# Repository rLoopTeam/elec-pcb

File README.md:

# elec-pcb
All PCB designs for rLoop in Altium Designer 13 format.

Altium Viewer License is needed: http://www.altium.com/altium-designer-viewer
CAD files in Inventor 2013 format and .step.

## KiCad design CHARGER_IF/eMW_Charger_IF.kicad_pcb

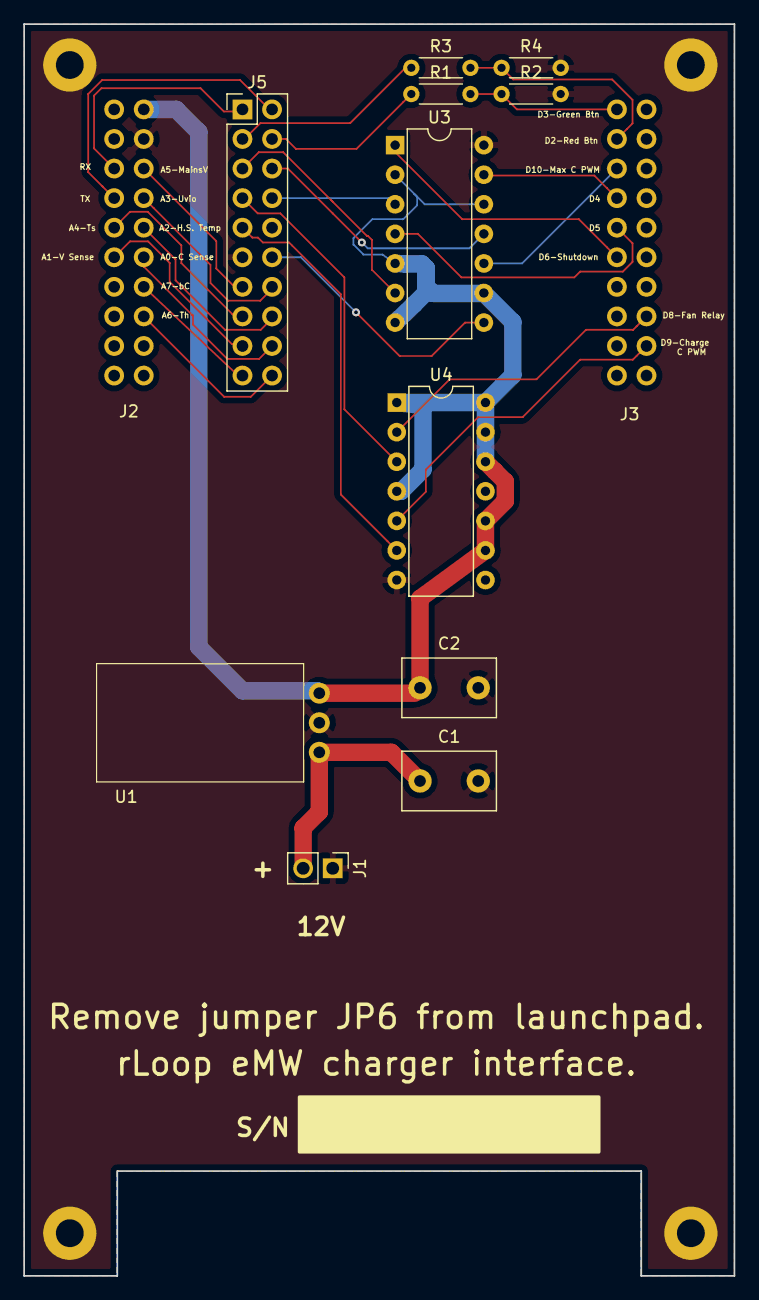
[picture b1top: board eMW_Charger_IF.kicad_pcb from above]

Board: 2 copper layers, 61.0 x 107.5 mm, 13 parts (0 on the bottom side), 29 nets.

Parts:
C1: 10 uF / 25V / TH; C_Disc_D8.0mm_W5.0mm_P5.00mm
C2: 22 uF / 16V / TH; C_Disc_D8.0mm_W5.0mm_P5.00mm
J1: CONN_01X02; Pin_Header_Straight_1x02_Pitch2.54mm
J2: Booster_J1_J3; 6-146256-0
J3: Booster_J4_J2; 6-146256-0_40-31_20_11
J5: CONN_02X10; Pin_Header_Straight_2x10_Pitch2.54mm
R1, R3: 10k / 10% / TH; R_Axial_DIN0204_L3.6mm_D1.6mm_P5.08mm_Horizontal
R2, R4: 20k / 10% / TH; R_Axial_DIN0204_L3.6mm_D1.6mm_P5.08mm_Horizontal
U1: V7805-2000R
U3, U4: SN74ACT08N; DIP-14_W7.62mm

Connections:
+5V: C2.1, J2.21, U1.3, U3.2, U3.5, U3.7, U3.9, U3.12, U4.1, U4.4, U4.9, U4.10, U4.12, U4.13, U4.14
+12V: C1.1, J1.2, U1.1
GND: C1.2, C2.2, J1.1, J2.22, J5.10, J5.11, R2.2, R4.2, U1.2, U3.14, U4.7
unnamed: J2.3, J5.1
unnamed: J2.4, J5.2
unnamed: J2.5, J5.15
unnamed: J2.6, J5.17
unnamed: J2.23, J5.13
unnamed: J2.24, J5.14
unnamed: J2.25, J5.16
unnamed: J2.26, J5.18
unnamed: J2.27, J5.19
unnamed: J2.28, J5.20
unnamed: J3.12, U4.5
unnamed: J3.13, U4.2
unnamed: J3.35, U3.1
unnamed: J3.36, U3.4
unnamed: J3.37, U3.13
unnamed: J3.38, U3.10
unnamed: J3.39, R3.2, R4.1
unnamed: J3.40, R1.2, R2.1
unnamed: J5.3, R3.1
unnamed: J5.4, R1.1
unnamed: J5.5, U3.6
unnamed: J5.6, U3.11
unnamed: J5.7, U4.3
unnamed: J5.8, U3.3
unnamed: J5.9, U4.6
unnamed: J5.12, U3.8

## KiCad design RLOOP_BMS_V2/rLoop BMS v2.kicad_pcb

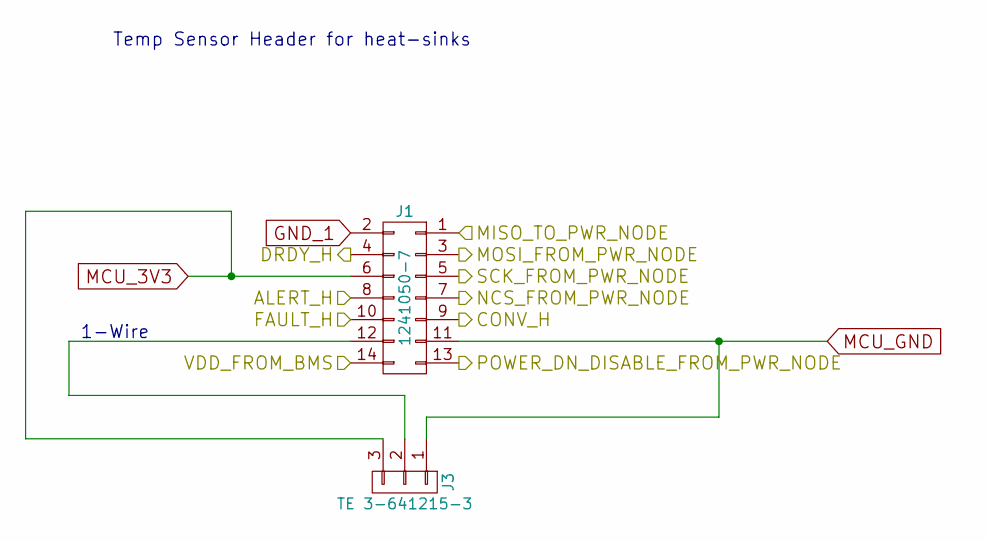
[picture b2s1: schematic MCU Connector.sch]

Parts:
J1: 1241050-7; Pin_Header_Straight_2x07_Pitch2.54mm_SMD_MIRROR
J3: TE 3-641215-3; 3-641215-3_3Pin_Latching_Header

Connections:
/CONTROLLER 1/ALERT_H: J1.8; also elsewhere on the board
/CONTROLLER 1/CONV_H: J1.9; also elsewhere on the board
/CONTROLLER 1/CS_H: J1.7; also elsewhere on the board
/CONTROLLER 1/DRDY_H: J1.4; also elsewhere on the board
/CONTROLLER 1/FAULT_H: J1.10; also elsewhere on the board
/ISO POWER/5V_ISO: J1.14; also elsewhere on the board
/ISO POWER/COMMS_EN: J1.13; also elsewhere on the board
/MCU Connector/MISO_TO_PWR_NODE: J1.1; also elsewhere on the board
/MCU Connector/MOSI_FROM_PWR_NODE: J1.3; also elsewhere on the board
/MCU Connector/SCK_FROM_PWR_NODE: J1.5; also elsewhere on the board
GND_1: J1.2; also elsewhere on the board
MCU_3V3: J1.6, J3.3; also elsewhere on the board
MCU_GND: J1.11, J3.1; also elsewhere on the board
unnamed: J1.12, J3.2

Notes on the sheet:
1-Wire
Temp Sensor Header for heat-sinks

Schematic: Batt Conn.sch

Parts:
J2: 2-640387-0; TE_2-640387-0

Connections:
/DISCHARGE_1/CELL_1: J2.2; also elsewhere on the board
/DISCHARGE_1/CELL_2: J2.3; also elsewhere on the board
/DISCHARGE_1/CELL_3: J2.4; also elsewhere on the board
/DISCHARGE_1/CELL_4: J2.5; also elsewhere on the board
/DISCHARGE_1/CELL_5: J2.6; also elsewhere on the board
/DISCHARGE_2/CELL_1: J2.8; also elsewhere on the board
/DISCHARGE_2/CELL_2: J2.9; also elsewhere on the board
/DISCHARGE_2/CELL_3: J2.10; also elsewhere on the board
GND_1: J2.1; also elsewhere on the board
GND_2: J2.7; also elsewhere on the board

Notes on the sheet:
Cell 0 is the negative terminal of the battery pack.

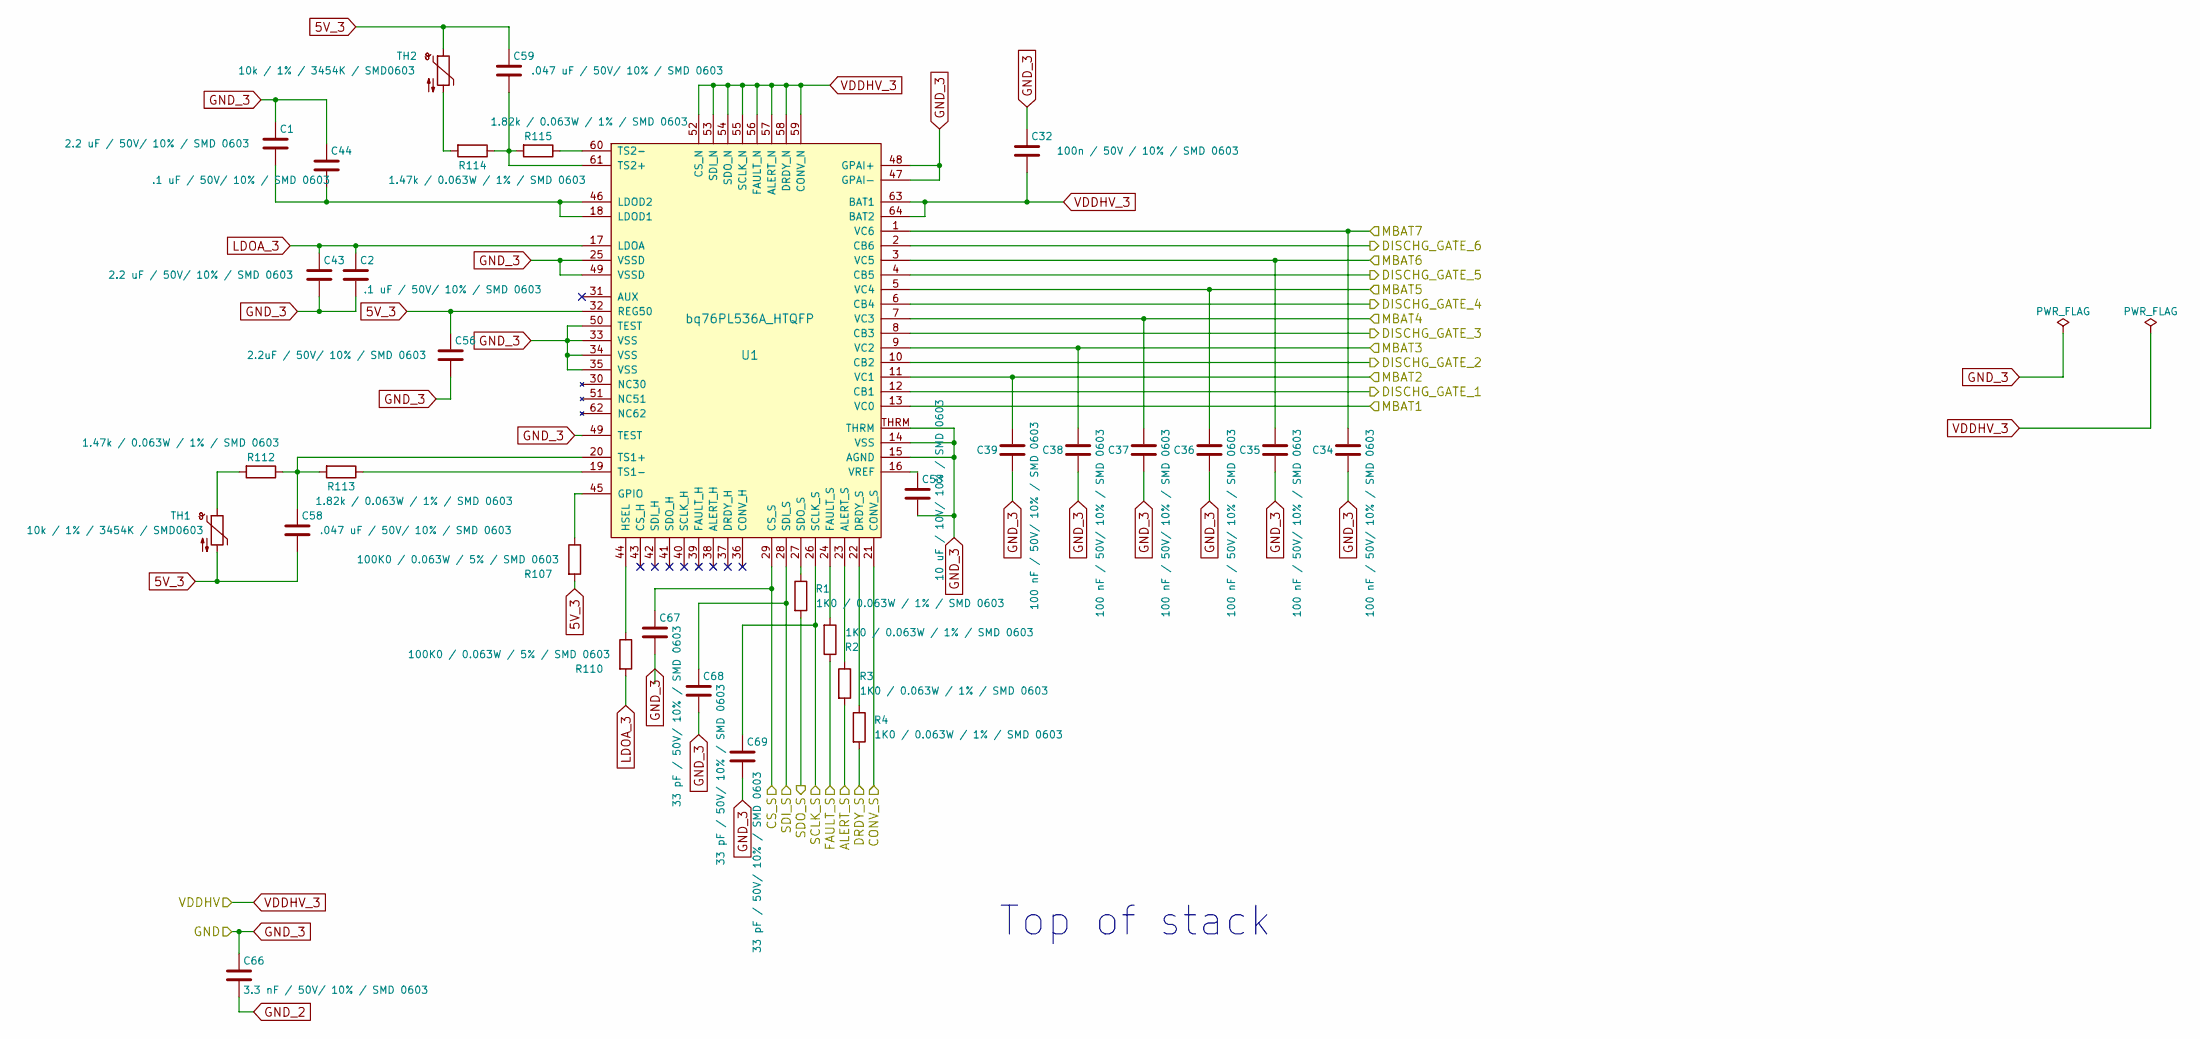
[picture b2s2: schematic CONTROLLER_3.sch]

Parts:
C1, C43: 2.2 uF / 50V/ 10% / SMD 0603; C_0603
C2, C44: .1 uF / 50V/ 10% / SMD 0603; C_0603
C32: 100n / 50V / 10% / SMD 0603; C_0603
C34, C35, C36, C37, C38, C39: 100 nF / 50V/ 10% / SMD 0603; C_0603
C53: 10 uF / 10V/ 10% / SMD 0603; C_0603
C56: 2.2uF / 50V/ 10% / SMD 0603; C_0603
C58, C59: .047 uF / 50V/ 10% / SMD 0603; C_0603
C66: 3.3 nF / 50V/ 10% / SMD 0603; C_0603
C67, C68, C69: 33 pF / 50V/ 10% / SMD 0603; C_0603
R1, R2, R3, R4: 1K0 / 0.063W / 1% / SMD 0603; R_0603
R107, R110: 100K0 / 0.063W / 5% / SMD 0603; R_0603
R112, R114: 1.47k / 0.063W / 1% / SMD 0603; R_0603
R113, R115: 1.82k / 0.063W / 1% / SMD 0603; R_0603
TH1, TH2: 10k / 1% / 3454K / SMD0603; R_0603
U1: bq76PL536A_HTQFP; bq76pl536a

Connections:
5V_3: C56.1, C58.2, C59.1, R107.2, TH1.2, TH2.1, U1.32 (REG50)
/CONTROLLER 2/ALERT_N: R3.2; also elsewhere on the board
/CONTROLLER 2/CONV_N: U1.21 (CONV_S); also elsewhere on the board
/CONTROLLER 2/CS_N: C67.1, U1.29 (CS_S); also elsewhere on the board
/CONTROLLER 2/DRDY_N: R4.2; also elsewhere on the board
/CONTROLLER 2/FAULT_N: R2.1; also elsewhere on the board
/CONTROLLER 2/SCLK_N: C69.1, U1.26 (SCLK_S); also elsewhere on the board
/CONTROLLER 2/SDI_N: C68.1, U1.28 (SDI_S); also elsewhere on the board
/CONTROLLER 2/SDO_N: R1.2; also elsewhere on the board
/CONTROLLER 3/MBAT2: C39.1, U1.11 (VC1); also elsewhere on the board
/CONTROLLER 3/MBAT3: C38.1, U1.9 (VC2); also elsewhere on the board
/CONTROLLER 3/MBAT4: C37.1, U1.7 (VC3); also elsewhere on the board
/CONTROLLER 3/MBAT5: C36.1, U1.5 (VC4); also elsewhere on the board
/CONTROLLER 3/MBAT6: C35.1, U1.3 (VC5); also elsewhere on the board
/CONTROLLER 3/MBAT7: C34.1, U1.1 (VC6); also elsewhere on the board
/DISCHARGE_3/DISCHARGE_1: U1.12 (CB1); also elsewhere on the board
/DISCHARGE_3/DISCHARGE_2: U1.10 (CB2); also elsewhere on the board
/DISCHARGE_3/DISCHARGE_3: U1.8 (CB3); also elsewhere on the board
/DISCHARGE_3/DISCHARGE_4: U1.6 (CB4); also elsewhere on the board
/DISCHARGE_3/DISCHARGE_5: U1.4 (CB5); also elsewhere on the board
/DISCHARGE_3/DISCHARGE_6: U1.2 (CB6); also elsewhere on the board
GND_2: C66.2; also elsewhere on the board
GND_3: C1.1, C2.2, C32.1, C34.2, C35.2, C36.2, C37.2, C38.2, C39.2, C43.2, C44.1, C53.2, C56.2, C66.1, C67.2, C68.2, C69.2, U1.13 (VC0), U1.14 (VSS), U1.15 (AGND), U1.25 (VSSD), U1.33 (VSS), U1.34 (VSS), U1.35 (VSS), U1.47 (GPAI-), U1.48 (GPAI+), U1.49 (TEST), U1.50 (TEST), U1.THRM; also elsewhere on the board
LDOA_3: C2.1, C43.1, R110.2, U1.17 (LDOA)
unnamed: C1.2, C44.2, U1.18 (LDOD1), U1.46 (LDOD2)
unnamed: C53.1, U1.16 (VREF)
unnamed: C58.1, R112.1, R113.2, U1.20 (TS1+)
unnamed: C59.2, R114.1, R115.2, U1.61 (TS2+)
unnamed: R1.1, U1.27 (SDO_S)
unnamed: R2.2, U1.24 (FAULT_S)
unnamed: R3.1, U1.23 (ALERT_S)
unnamed: R4.1, U1.22 (DRDY_S)
unnamed: R107.1, U1.45 (GPIO)
unnamed: R110.1, U1.44 (HSEL)
unnamed: R112.2, TH1.1
unnamed: R113.1, U1.19 (TS1-)
unnamed: R114.2, TH2.2
unnamed: R115.1, U1.60 (TS2-)
VDDHV_3: C32.2, U1.52 (CS_N), U1.53 (SDI_N), U1.54 (SDO_N), U1.55 (SCLK_N), U1.56 (FAULT_N), U1.57 (ALERT_N), U1.58 (DRDY_N), U1.59 (CONV_N), U1.63 (BAT1), U1.64 (BAT2); also elsewhere on the board

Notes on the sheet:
Top of stack

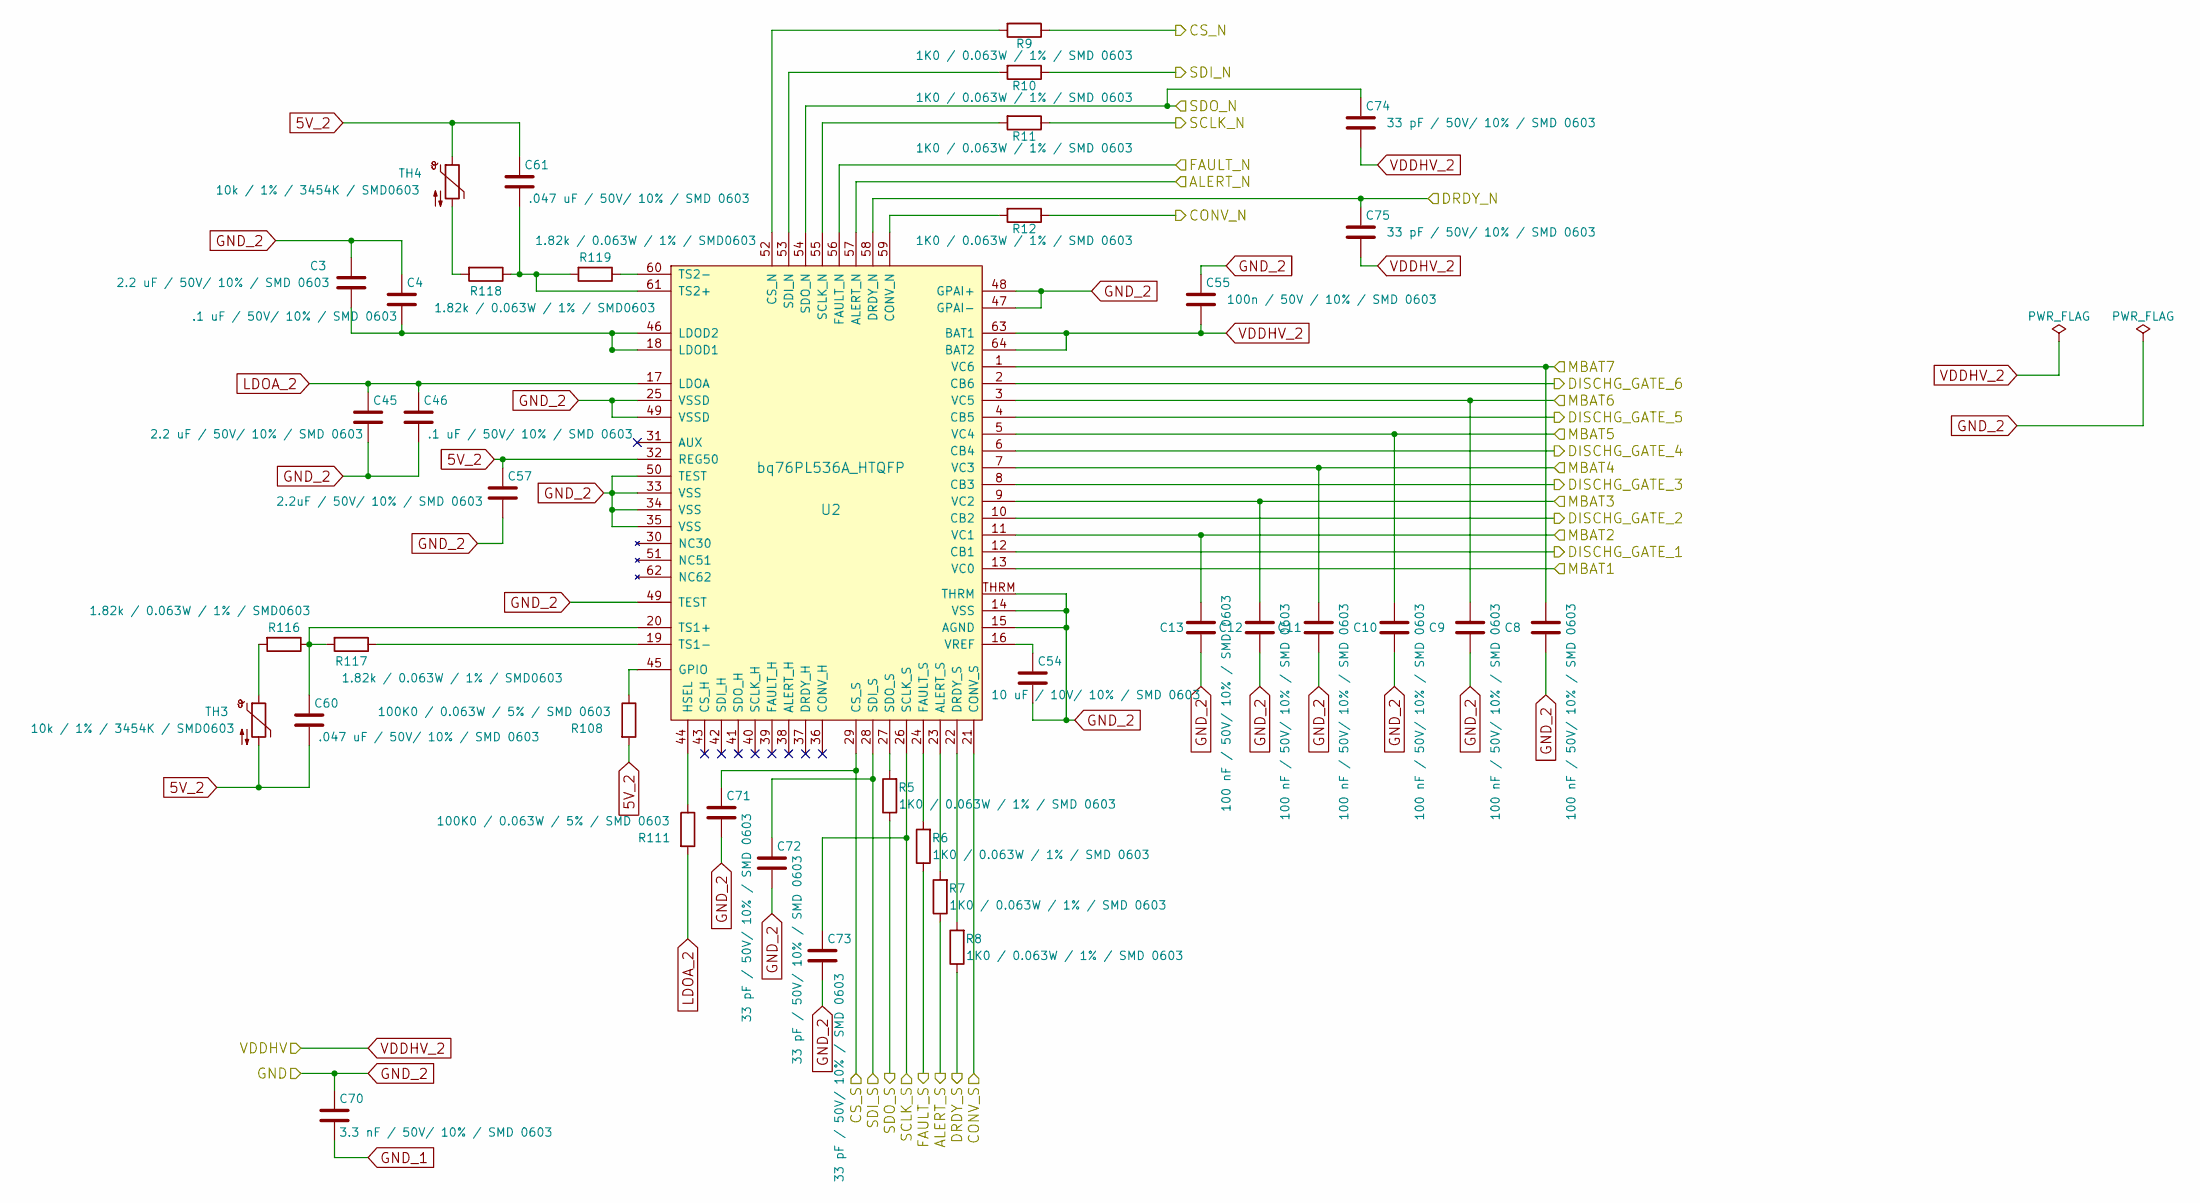
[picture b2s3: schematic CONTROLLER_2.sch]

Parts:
C3, C45: 2.2 uF / 50V/ 10% / SMD 0603; C_0603
C4, C46: .1 uF / 50V/ 10% / SMD 0603; C_0603
C8, C9, C10, C11, C12, C13: 100 nF / 50V/ 10% / SMD 0603; C_0603
C54: 10 uF / 10V/ 10% / SMD 0603; C_0603
C55: 100n / 50V / 10% / SMD 0603; C_0603
C57: 2.2uF / 50V/ 10% / SMD 0603; C_0603
C60, C61: .047 uF / 50V/ 10% / SMD 0603; C_0603
C70: 3.3 nF / 50V/ 10% / SMD 0603; C_0603
C71, C72, C73, C74, C75: 33 pF / 50V/ 10% / SMD 0603; C_0603
R5, R6, R7, R8, R9, R10, R11, R12: 1K0 / 0.063W / 1% / SMD 0603; R_0603
R108, R111: 100K0 / 0.063W / 5% / SMD 0603; R_0603
R116, R117, R118, R119: 1.82k / 0.063W / 1% / SMD0603; R_0603
TH3, TH4: 10k / 1% / 3454K / SMD0603; R_0603
U2: bq76PL536A_HTQFP; bq76pl536a

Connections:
5V_2: C57.1, C60.2, C61.1, R108.2, TH3.2, TH4.1, U2.32 (REG50)
/CONTROLLER 1/ALERT_N: R7.1; also elsewhere on the board
/CONTROLLER 1/CONV_N: U2.21 (CONV_S); also elsewhere on the board
/CONTROLLER 1/CS_N: C71.1, U2.29 (CS_S); also elsewhere on the board
/CONTROLLER 1/DRDY_N: R8.1; also elsewhere on the board
/CONTROLLER 1/FAULT_N: R6.1; also elsewhere on the board
/CONTROLLER 1/SCLK_N: C73.1, U2.26 (SCLK_S); also elsewhere on the board
/CONTROLLER 1/SDI_N: C72.1, U2.28 (SDI_S); also elsewhere on the board
/CONTROLLER 1/SDO_N: R5.1; also elsewhere on the board
/CONTROLLER 2/ALERT_N: U2.57 (ALERT_N); also elsewhere on the board
/CONTROLLER 2/CONV_N: R12.1; also elsewhere on the board
/CONTROLLER 2/CS_N: R9.1; also elsewhere on the board
/CONTROLLER 2/DRDY_N: C75.1, U2.58 (DRDY_N); also elsewhere on the board
/CONTROLLER 2/FAULT_N: U2.56 (FAULT_N); also elsewhere on the board
/CONTROLLER 2/MBAT2: C13.1, U2.11 (VC1); also elsewhere on the board
/CONTROLLER 2/MBAT3: C12.1, U2.9 (VC2); also elsewhere on the board
/CONTROLLER 2/MBAT4: C11.1, U2.7 (VC3); also elsewhere on the board
/CONTROLLER 2/MBAT5: C10.1, U2.5 (VC4); also elsewhere on the board
/CONTROLLER 2/MBAT6: C9.1, U2.3 (VC5); also elsewhere on the board
/CONTROLLER 2/MBAT7: C8.1, U2.1 (VC6); also elsewhere on the board
/CONTROLLER 2/SCLK_N: R11.1; also elsewhere on the board
/CONTROLLER 2/SDI_N: R10.1; also elsewhere on the board
/CONTROLLER 2/SDO_N: C74.1, U2.54 (SDO_N); also elsewhere on the board
/DISCHARGE_2/DISCHARGE_1: U2.12 (CB1); also elsewhere on the board
/DISCHARGE_2/DISCHARGE_2: U2.10 (CB2); also elsewhere on the board
/DISCHARGE_2/DISCHARGE_3: U2.8 (CB3); also elsewhere on the board
/DISCHARGE_2/DISCHARGE_4: U2.6 (CB4); also elsewhere on the board
/DISCHARGE_2/DISCHARGE_5: U2.4 (CB5); also elsewhere on the board
/DISCHARGE_2/DISCHARGE_6: U2.2 (CB6); also elsewhere on the board
GND_1: C70.2; also elsewhere on the board
GND_2: C3.1, C4.1, C8.2, C9.2, C10.2, C11.2, C12.2, C13.2, C45.2, C46.2, C54.2, C55.1, C57.2, C70.1, C71.2, C72.2, C73.2, U2.13 (VC0), U2.14 (VSS), U2.15 (AGND), U2.25 (VSSD), U2.33 (VSS), U2.34 (VSS), U2.35 (VSS), U2.47 (GPAI-), U2.48 (GPAI+), U2.49 (TEST), U2.50 (TEST), U2.THRM; also elsewhere on the board
GND_3: C55.2, C74.2, C75.2, U2.63 (BAT1), U2.64 (BAT2); also elsewhere on the board
LDOA_2: C45.1, C46.1, R111.2, U2.17 (LDOA)
unnamed: C3.2, C4.2, U2.18 (LDOD1), U2.46 (LDOD2)
unnamed: C54.1, U2.16 (VREF)
unnamed: C60.1, R116.1, R117.2, U2.20 (TS1+)
unnamed: C61.2, R118.1, R119.2, U2.61 (TS2+)
unnamed: R5.2, U2.27 (SDO_S)
unnamed: R6.2, U2.24 (FAULT_S)
unnamed: R7.2, U2.23 (ALERT_S)
unnamed: R8.2, U2.22 (DRDY_S)
unnamed: R9.2, U2.52 (CS_N)
unnamed: R10.2, U2.53 (SDI_N)
unnamed: R11.2, U2.55 (SCLK_N)
unnamed: R12.2, U2.59 (CONV_N)
unnamed: R108.1, U2.45 (GPIO)
unnamed: R111.1, U2.44 (HSEL)
unnamed: R116.2, TH3.1
unnamed: R117.1, U2.19 (TS1-)
unnamed: R118.2, TH4.2
unnamed: R119.1, U2.60 (TS2-)

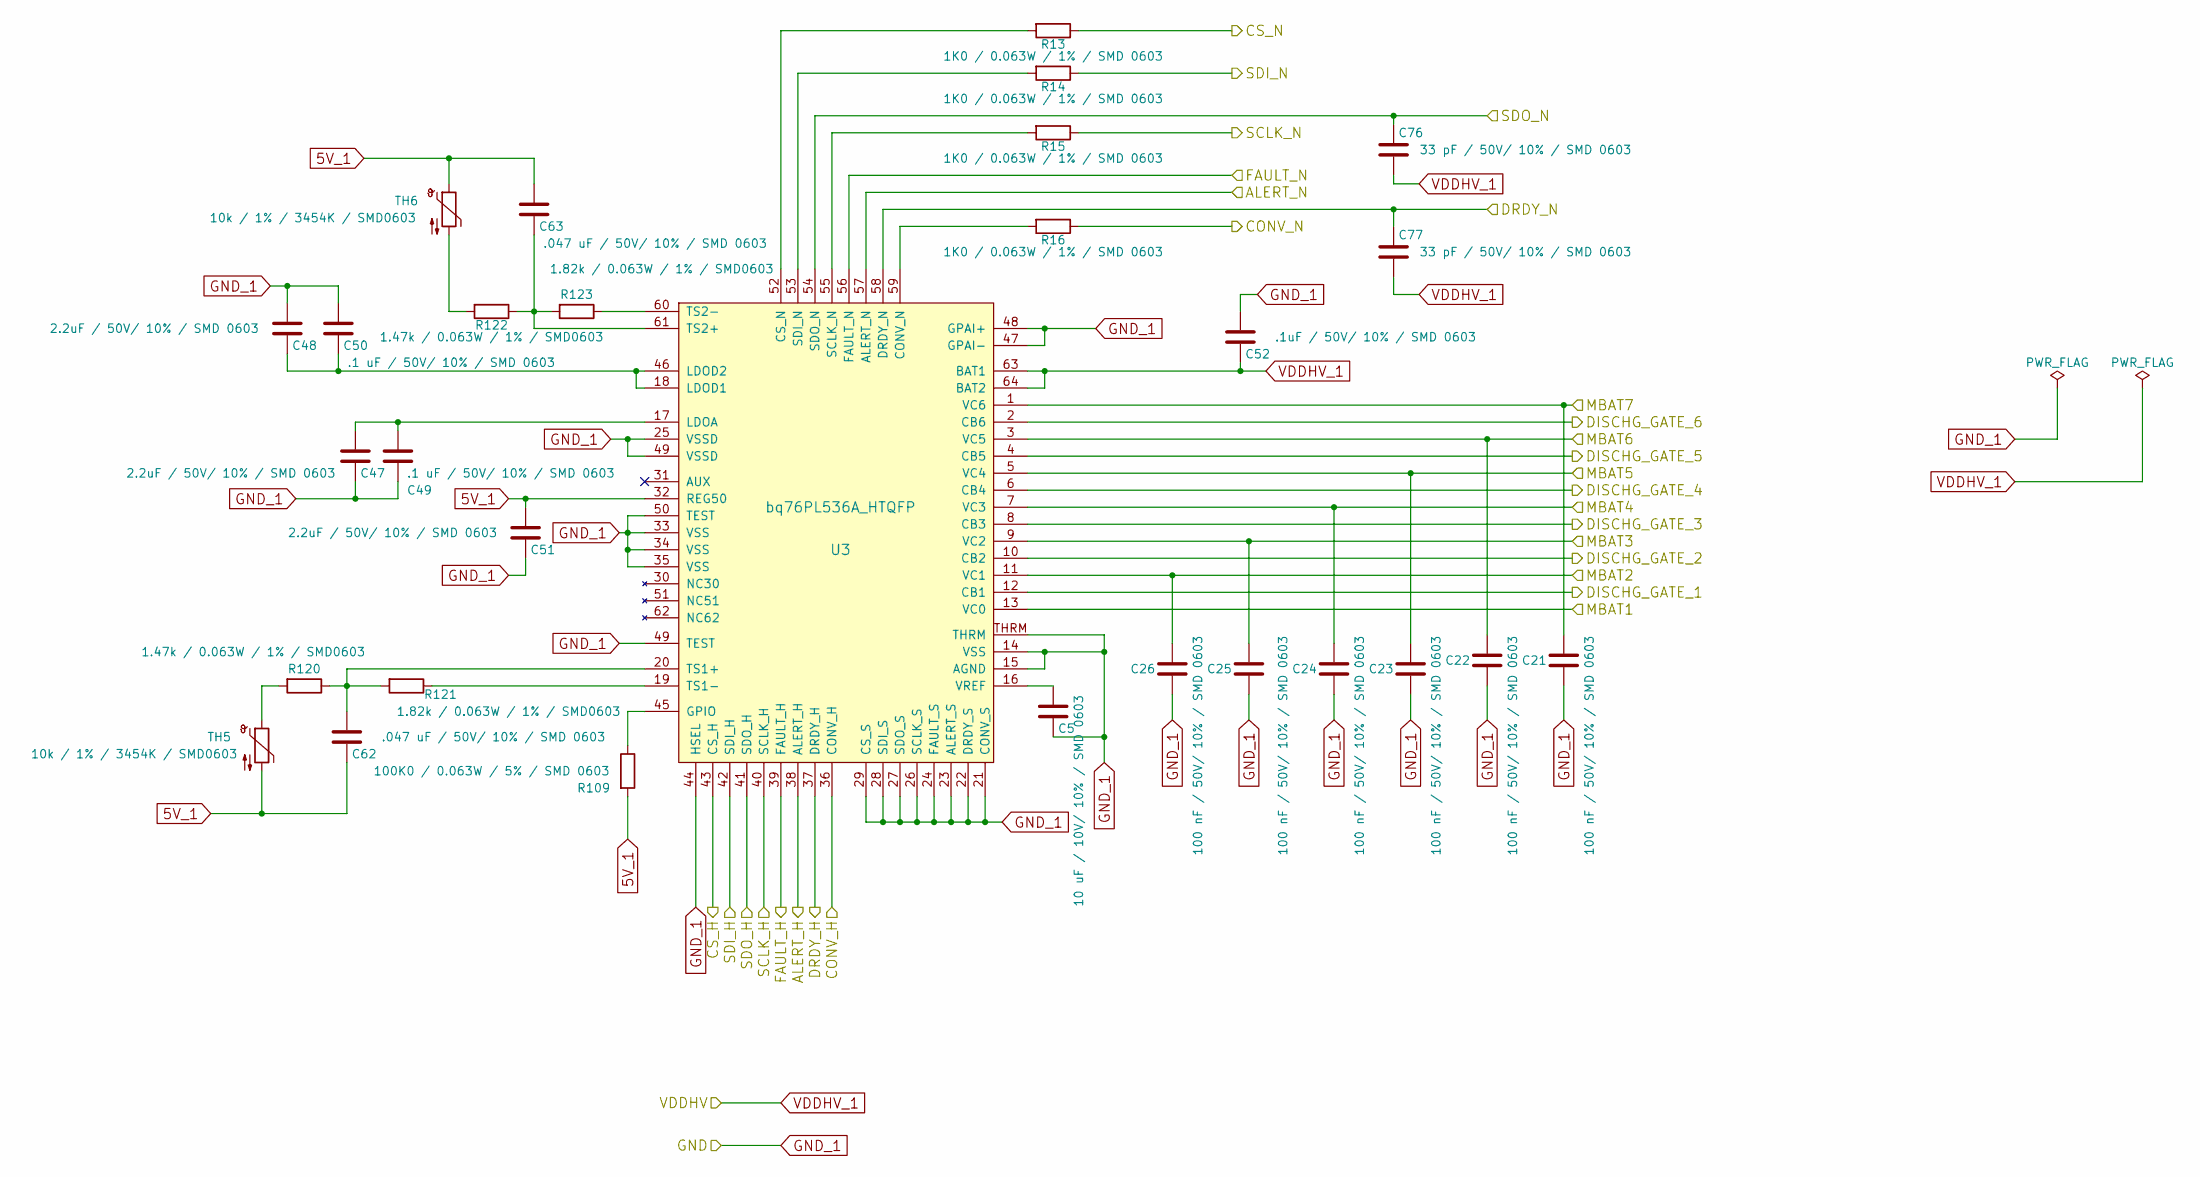
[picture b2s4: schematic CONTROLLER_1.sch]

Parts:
C5: 10 uF / 10V/ 10% / SMD 0603; C_0603
C21, C22, C23, C24, C25, C26: 100 nF / 50V/ 10% / SMD 0603; C_0603
C47, C48, C51: 2.2uF / 50V/ 10% / SMD 0603; C_0603
C49, C50: .1 uF / 50V/ 10% / SMD 0603; C_0603
C52: .1uF / 50V/ 10% / SMD 0603; C_0603
C62, C63: .047 uF / 50V/ 10% / SMD 0603; C_0603
C76, C77: 33 pF / 50V/ 10% / SMD 0603; C_0603
R13, R14, R15, R16: 1K0 / 0.063W / 1% / SMD 0603; R_0603
R109: 100K0 / 0.063W / 5% / SMD 0603; R_0603
R120, R122: 1.47k / 0.063W / 1% / SMD0603; R_0603
R121, R123: 1.82k / 0.063W / 1% / SMD0603; R_0603
TH5, TH6: 10k / 1% / 3454K / SMD0603; R_0603
U3: bq76PL536A_HTQFP; bq76pl536a

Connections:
5V_1: C51.2, C62.1, C63.2, R109.2, TH5.2, TH6.1, U3.32 (REG50)
/CONTROLLER 1/ALERT_H: U3.38 (ALERT_H); also elsewhere on the board
/CONTROLLER 1/ALERT_N: U3.57 (ALERT_N); also elsewhere on the board
/CONTROLLER 1/CONV_H: U3.36 (CONV_H); also elsewhere on the board
/CONTROLLER 1/CONV_N: R16.1; also elsewhere on the board
/CONTROLLER 1/CS_H: U3.43 (CS_H); also elsewhere on the board
/CONTROLLER 1/CS_N: R13.1; also elsewhere on the board
/CONTROLLER 1/DRDY_H: U3.37 (DRDY_H); also elsewhere on the board
/CONTROLLER 1/DRDY_N: C77.1, U3.58 (DRDY_N); also elsewhere on the board
/CONTROLLER 1/FAULT_H: U3.39 (FAULT_H); also elsewhere on the board
/CONTROLLER 1/FAULT_N: U3.56 (FAULT_N); also elsewhere on the board
/CONTROLLER 1/MBAT2: C26.1, U3.11 (VC1); also elsewhere on the board
/CONTROLLER 1/MBAT3: C25.1, U3.9 (VC2); also elsewhere on the board
/CONTROLLER 1/MBAT4: C24.1, U3.7 (VC3); also elsewhere on the board
/CONTROLLER 1/MBAT5: C23.1, U3.5 (VC4); also elsewhere on the board
/CONTROLLER 1/MBAT6: C22.1, U3.3 (VC5); also elsewhere on the board
/CONTROLLER 1/MBAT7: C21.1, U3.1 (VC6); also elsewhere on the board
/CONTROLLER 1/SCLK_N: R15.1; also elsewhere on the board
/CONTROLLER 1/SDI_N: R14.1; also elsewhere on the board
/CONTROLLER 1/SDO_N: C76.1, U3.54 (SDO_N); also elsewhere on the board
/DISCHARGE_1/DISCHARGE_1: U3.12 (CB1); also elsewhere on the board
/DISCHARGE_1/DISCHARGE_2: U3.10 (CB2); also elsewhere on the board
/DISCHARGE_1/DISCHARGE_3: U3.8 (CB3); also elsewhere on the board
/DISCHARGE_1/DISCHARGE_4: U3.6 (CB4); also elsewhere on the board
/DISCHARGE_1/DISCHARGE_5: U3.4 (CB5); also elsewhere on the board
/DISCHARGE_1/DISCHARGE_6: U3.2 (CB6); also elsewhere on the board
/MCU Connector/MISO_TO_PWR_NODE: U3.41 (SDO_H); also elsewhere on the board
/MCU Connector/MOSI_FROM_PWR_NODE: U3.42 (SDI_H); also elsewhere on the board
/MCU Connector/SCK_FROM_PWR_NODE: U3.40 (SCLK_H); also elsewhere on the board
GND_1: C5.1, C21.2, C22.2, C23.2, C24.2, C25.2, C26.2, C47.1, C48.2, C49.1, C50.2, C51.1, C52.2, U3.13 (VC0), U3.14 (VSS), U3.15 (AGND), U3.21 (CONV_S), U3.22 (DRDY_S), U3.23 (ALERT_S), U3.24 (FAULT_S), U3.25 (VSSD), U3.26 (SCLK_S), U3.27 (SDO_S), U3.28 (SDI_S), U3.29 (CS_S), U3.33 (VSS), U3.34 (VSS), U3.35 (VSS), U3.44 (HSEL), U3.47 (GPAI-), U3.48 (GPAI+), U3.49 (TEST), U3.50 (TEST), U3.THRM; also elsewhere on the board
GND_2: C52.1, C76.2, C77.2, U3.63 (BAT1), U3.64 (BAT2); also elsewhere on the board
unnamed: C5.2, U3.16 (VREF)
unnamed: C47.2, C49.2, U3.17 (LDOA)
unnamed: C48.1, C50.1, U3.18 (LDOD1), U3.46 (LDOD2)
unnamed: C62.2, R120.1, R121.2, U3.20 (TS1+)
unnamed: C63.1, R122.1, R123.2, U3.61 (TS2+)
unnamed: R13.2, U3.52 (CS_N)
unnamed: R14.2, U3.53 (SDI_N)
unnamed: R15.2, U3.55 (SCLK_N)
unnamed: R16.2, U3.59 (CONV_N)
unnamed: R109.1, U3.45 (GPIO)
unnamed: R120.2, TH5.1
unnamed: R121.1, U3.19 (TS1-)
unnamed: R122.2, TH6.2
unnamed: R123.1, U3.60 (TS2-)

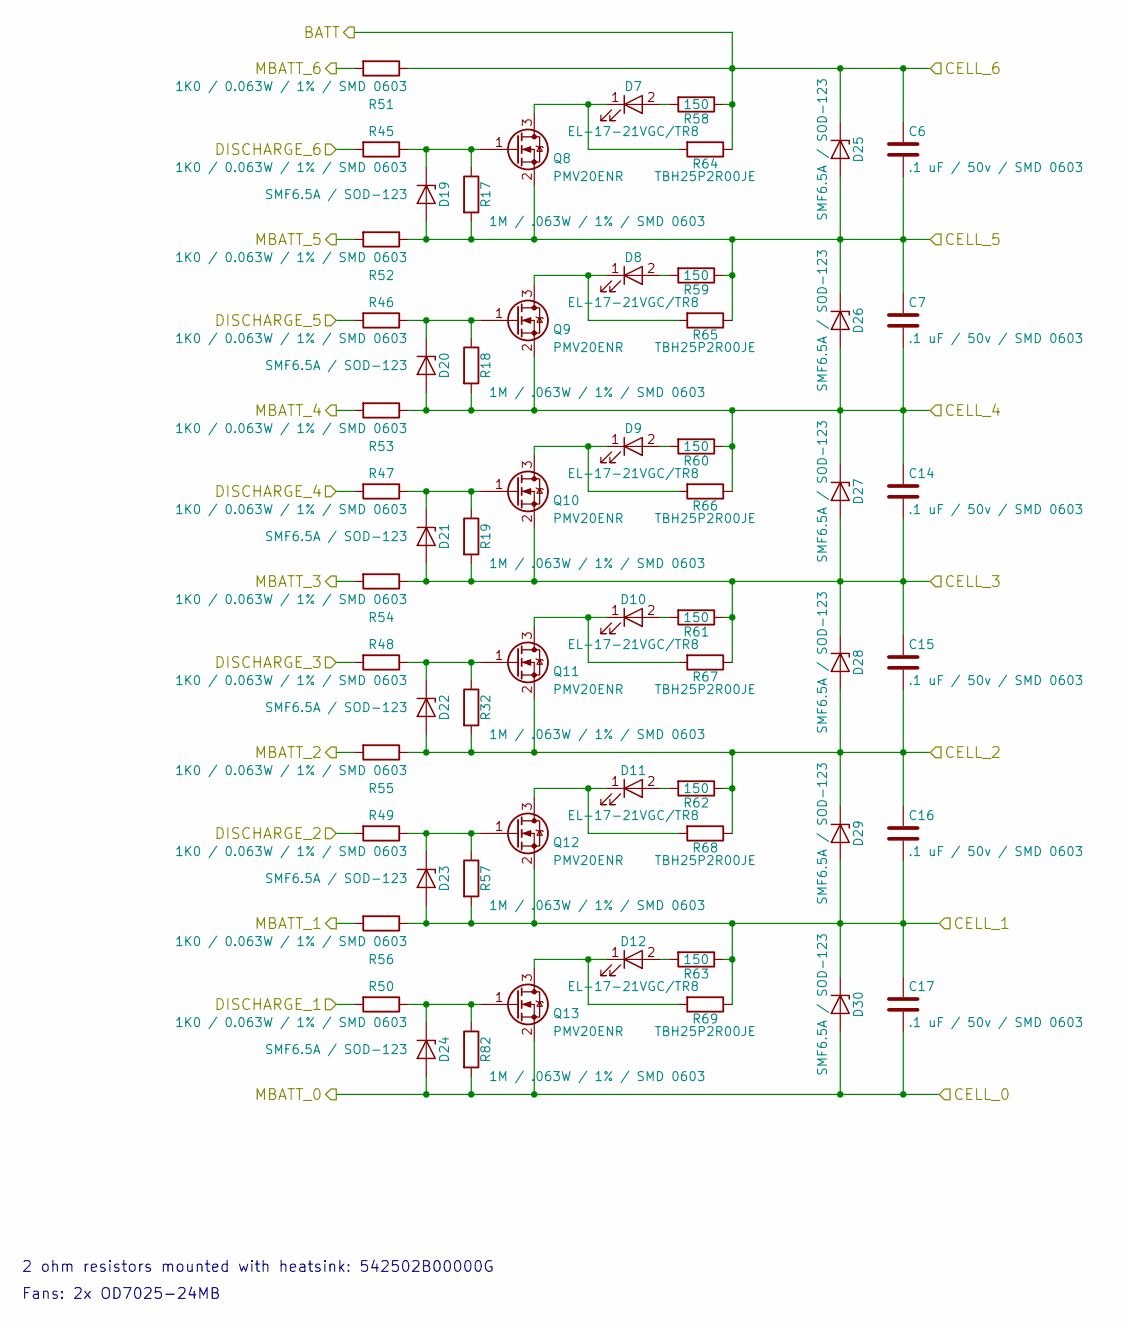
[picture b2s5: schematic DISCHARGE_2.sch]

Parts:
C6, C7, C14, C15, C16, C17: .1 uF / 50v / SMD 0603; C_0603
D7, D8, D9, D10, D11, D12: EL-17-21VGC/TR8; LED_0805
D19, D20, D21, D22, D23, D24, D25, D26, D27, D28, D29, D30: SMF6.5A / SOD-123; D_SOD-123
Q8, Q9, Q10, Q11, Q12, Q13: PMV20ENR; PMV20ENR-TO_236AB
R17, R18, R19, R32, R57, R82: 1M / .063W / 1% / SMD 0603; R_0603
R45, R46, R47, R48, R49, R50, R51, R52, R53, R54, R55, R56: 1K0 / 0.063W / 1% / SMD 0603; R_0603
R58, R59, R60, R61, R62, R63: 150; R_0603
R64, R65, R66, R67, R68, R69: TBH25P2R00JE; 2-OHM-TO-220-TBH25P2R00JE

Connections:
/CONTROLLER 2/MBAT2: R56.2; also elsewhere on the board
/CONTROLLER 2/MBAT3: R55.2; also elsewhere on the board
/CONTROLLER 2/MBAT4: R54.2; also elsewhere on the board
/CONTROLLER 2/MBAT5: R53.2; also elsewhere on the board
/CONTROLLER 2/MBAT6: R52.2; also elsewhere on the board
/CONTROLLER 2/MBAT7: R51.2; also elsewhere on the board
/DISCHARGE_2/CELL_1: C16.2, C17.1, D23.2 (A), D29.2 (A), D30.1 (K), Q12.2 (S), R56.1, R57.2, R63.1, R69.1; also elsewhere on the board
/DISCHARGE_2/CELL_2: C15.2, C16.1, D22.2 (A), D28.2 (A), D29.1 (K), Q11.2 (S), R32.2, R55.1, R62.1, R68.1; also elsewhere on the board
/DISCHARGE_2/CELL_3: C14.2, C15.1, D21.2 (A), D27.2 (A), D28.1 (K), Q10.2 (S), R19.2, R54.1, R61.1, R67.1; also elsewhere on the board
/DISCHARGE_2/CELL_4: C7.2, C14.1, D20.2 (A), D26.2 (A), D27.1 (K), Q9.2 (S), R18.2, R53.1, R60.1, R66.1; also elsewhere on the board
/DISCHARGE_2/CELL_5: C6.2, C7.1, D19.2 (A), D25.2 (A), D26.1 (K), Q8.2 (S), R17.2, R52.1, R59.1, R65.1; also elsewhere on the board
/DISCHARGE_2/DISCHARGE_1: R50.2; also elsewhere on the board
/DISCHARGE_2/DISCHARGE_2: R49.2; also elsewhere on the board
/DISCHARGE_2/DISCHARGE_3: R48.2; also elsewhere on the board
/DISCHARGE_2/DISCHARGE_4: R47.2; also elsewhere on the board
/DISCHARGE_2/DISCHARGE_5: R46.2; also elsewhere on the board
/DISCHARGE_2/DISCHARGE_6: R45.2; also elsewhere on the board
GND_2: C17.2, D24.2 (A), D30.2 (A), Q13.2 (S), R82.2; also elsewhere on the board
GND_3: C6.1, D25.1 (K), R51.1, R58.1, R64.1; also elsewhere on the board
unnamed: D7.1 (K), Q8.3 (D), R64.2
unnamed: D7.2 (A), R58.2
unnamed: D8.1 (K), Q9.3 (D), R65.2
unnamed: D8.2 (A), R59.2
unnamed: D9.1 (K), Q10.3 (D), R66.2
unnamed: D9.2 (A), R60.2
unnamed: D10.1 (K), Q11.3 (D), R67.2
unnamed: D10.2 (A), R61.2
unnamed: D11.1 (K), Q12.3 (D), R68.2
unnamed: D11.2 (A), R62.2
unnamed: D12.1 (K), Q13.3 (D), R69.2
unnamed: D12.2 (A), R63.2
unnamed: D19.1 (K), Q8.1 (G), R17.1, R45.1
unnamed: D20.1 (K), Q9.1 (G), R18.1, R46.1
unnamed: D21.1 (K), Q10.1 (G), R19.1, R47.1
unnamed: D22.1 (K), Q11.1 (G), R32.1, R48.1
unnamed: D23.1 (K), Q12.1 (G), R49.1, R57.1
unnamed: D24.1 (K), Q13.1 (G), R50.1, R82.1

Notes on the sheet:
2 ohm resistors mounted with heatsink: 542502B00000G
Fans: 2x OD7025-24MB
